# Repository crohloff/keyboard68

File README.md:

# keyboard68

## Production files
- The gerber files can be used with any manufacturer
- position files are meant to be used with jlcpcb and are already changed accordingly

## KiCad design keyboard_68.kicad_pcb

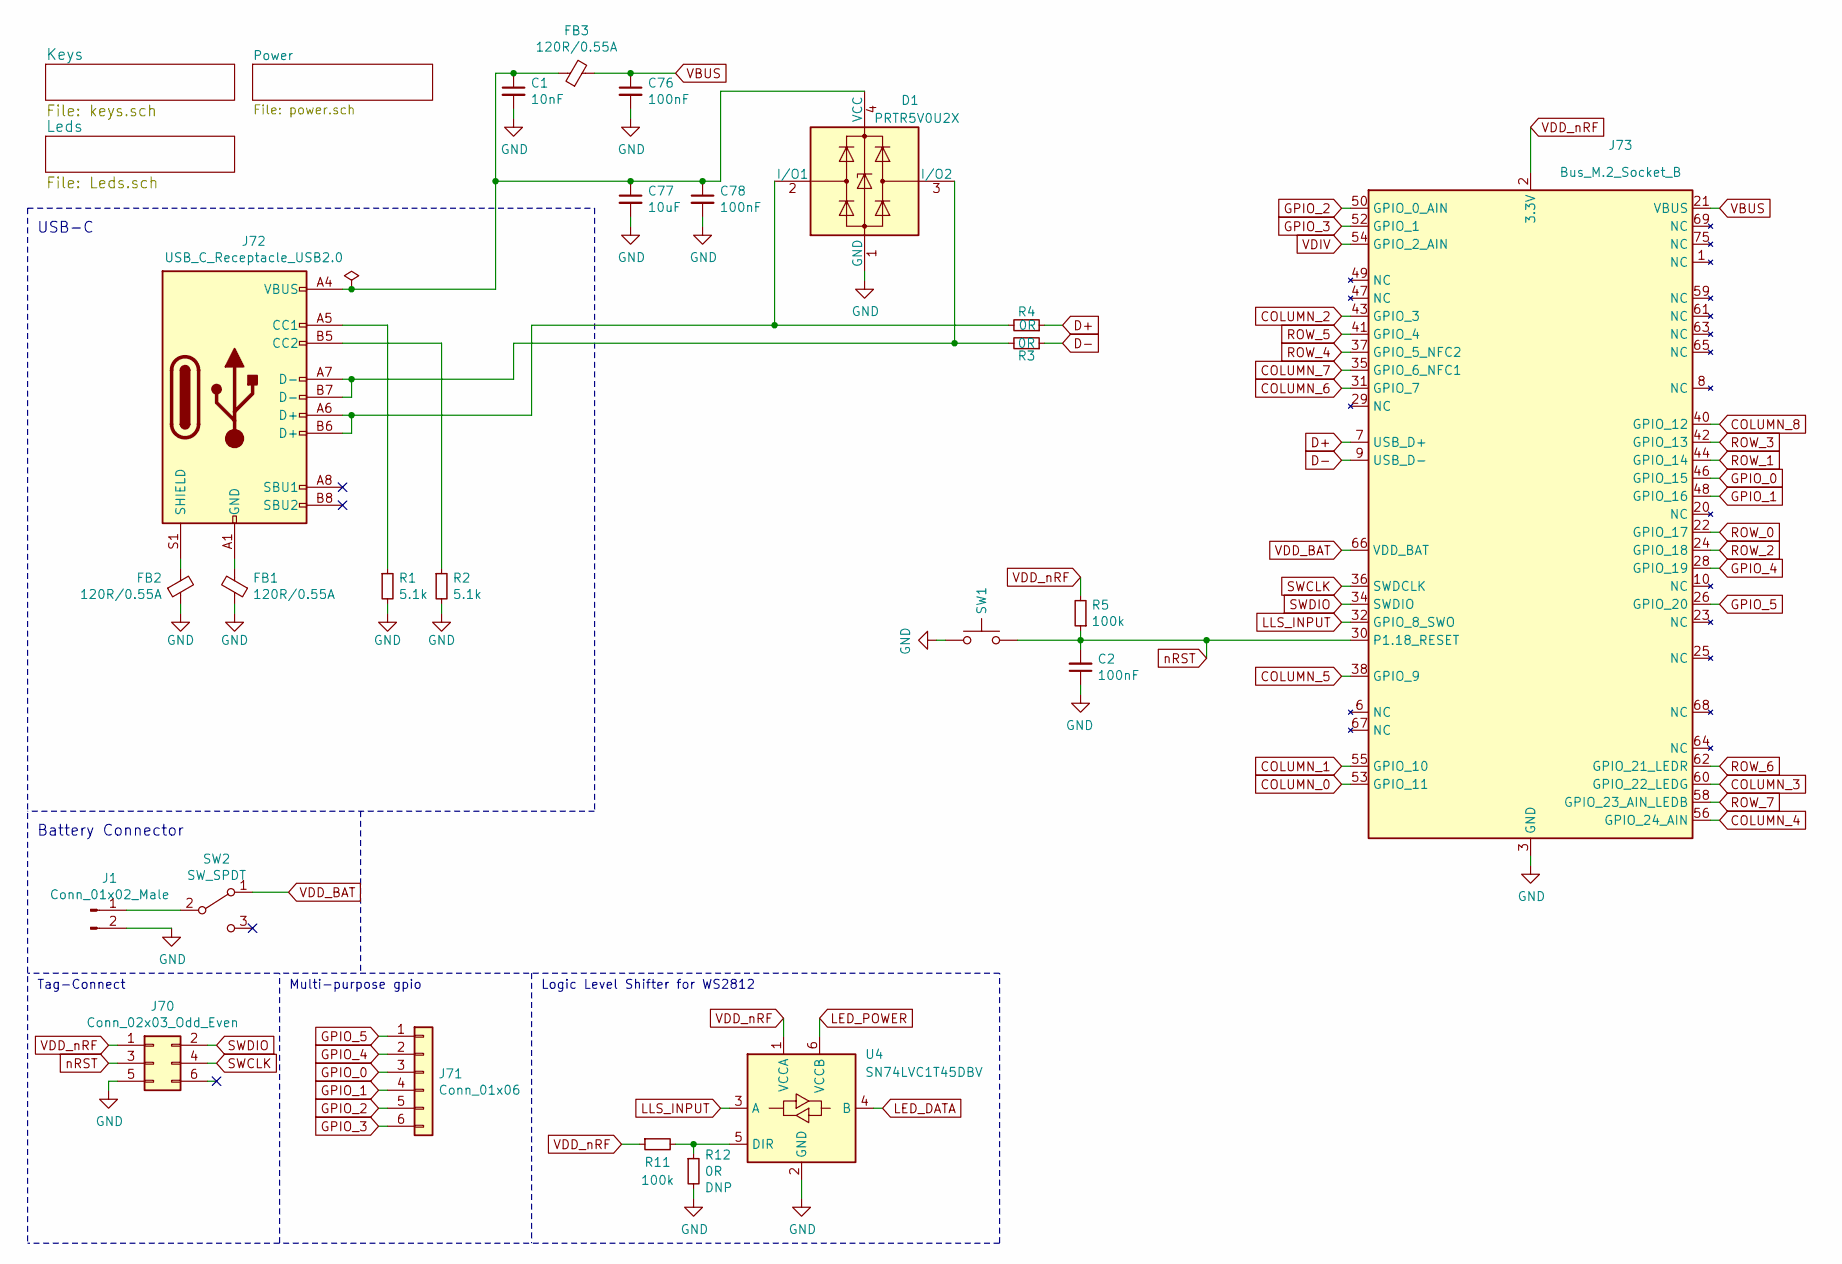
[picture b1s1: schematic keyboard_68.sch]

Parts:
C1: 10nF; C_0805_2012Metric; LCSC C83170
C2, C76, C78: 100nF; C_0805_2012Metric; LCSC C38141
C77: 10uF; C_0805_2012Metric; LCSC C307523
D1: PRTR5V0U2X; SOT-143; LCSC C330092
FB1, FB2, FB3: 120R/0.55A; L_0402_1005Metric; LCSC C85812
J1: Conn_01x02_Male; JST_PH_S2B-PH-SM4-TB_LF__SN_; MPN S2B-PH-SM4-TB(LF)(SN); DigiKey 455-1749-1-ND
J70: Conn_02x03_Odd_Even; Tag-Connect_TC2030-IDC-NL_2x03_P1.27mm_Vertical
J71: Conn_01x06; PinHeader_1x06_P2.54mm_Horizontal
J72: USB_C_Receptacle_USB2.0; USB_C_China; MPN U262-161N-4BVC11; LCSC C319148
J73: Bus_M.2_Socket_B; te_connectivity_121991190
R1, R2: 5.1k; R_0805_2012Metric; LCSC C84375
R3, R4, R12: 0R; R_0805_2012Metric; LCSC C96345
R5, R11: 100k; R_0805_2012Metric; LCSC C96346
SW1: EVQPUJ02K / EVQPUA02K; Panasonic_EVQPUJ_EVQPUA; MPN EVQ-PUJ02K; DigiKey P10851SCT-ND
SW2: SW_SPDT; SW_SPDT_CK-JS102011SAQN; MPN JS102011SAQN; DigiKey 401-1999-1-ND
U4: SN74LVC1T45DBV; SOT-23-6; MPN SN74LVC1T45DBVT; Digikey 296-30381-1-ND

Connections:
COLUMN_0: J73.53 (GPIO_11); also elsewhere on the board
COLUMN_1: J73.55 (GPIO_10); also elsewhere on the board
COLUMN_2: J73.43 (GPIO_3); also elsewhere on the board
COLUMN_3: J73.60 (GPIO_22_LEDG); also elsewhere on the board
COLUMN_4: J73.56 (GPIO_24_AIN); also elsewhere on the board
COLUMN_5: J73.38 (GPIO_9); also elsewhere on the board
COLUMN_6: J73.31 (GPIO_7); also elsewhere on the board
COLUMN_7: J73.35 (GPIO_6_NFC1); also elsewhere on the board
COLUMN_8: J73.40 (GPIO_12); also elsewhere on the board
D+: J73.7 (USB_D+), R4.1
D-: J73.9 (USB_D-), R3.1
GND: C1.2, C2.1, C76.2, C77.2, C78.2, D1.1 (GND), FB1.1, FB2.1, J1.2, J70.5, J73.3 (GND), J73.5 (GND), J73.11 (GND), J73.27 (GND), J73.33 (GND), J73.39 (GND), J73.45 (GND), J73.51 (GND), J73.57 (GND), J73.71 (GND), J73.73 (GND), R1.2, R2.2, R12.2, SW1.1, U4.2 (GND); also elsewhere on the board
GPIO_0: J71.3, J73.46 (GPIO_15)
GPIO_1: J71.4, J73.48 (GPIO_16)
GPIO_2: J71.5, J73.50 (GPIO_0_AIN)
GPIO_3: J71.6, J73.52 (GPIO_1)
GPIO_4: J71.2, J73.28 (GPIO_19)
GPIO_5: J71.1, J73.26 (GPIO_20)
LED_DATA: U4.4 (B); also elsewhere on the board
LED_POWER: U4.6 (VCCB); also elsewhere on the board
unnamed: C1.1, C77.1, C78.1, D1.4 (VCC), FB3.1, J72.A4 (VBUS), J72.A9 (VBUS), J72.B4 (VBUS), J72.B9 (VBUS)
unnamed: D1.2 (I/O1), J72.A6 (D+), J72.B6 (D+), R4.2
unnamed: D1.3 (I/O2), J72.A7 (D-), J72.B7 (D-), R3.2
unnamed: FB1.2, J72.A1 (GND), J72.A12 (GND), J72.B1 (GND), J72.B12 (GND)
unnamed: FB2.2, J72.S1 (SHIELD)
unnamed: J1.1, SW2.2 (B)
unnamed: J72.A5 (CC1), R1.1
unnamed: J72.B5 (CC2), R2.1
ROW_0: J73.22 (GPIO_17); also elsewhere on the board
ROW_1: J73.44 (GPIO_14); also elsewhere on the board
ROW_2: J73.24 (GPIO_18); also elsewhere on the board
ROW_3: J73.42 (GPIO_13); also elsewhere on the board
ROW_4: J73.37 (GPIO_5_NFC2); also elsewhere on the board
ROW_5: J73.41 (GPIO_4); also elsewhere on the board
ROW_6: J73.62 (GPIO_21_LEDR); also elsewhere on the board
ROW_7: J73.58 (GPIO_23_AIN_LEDB); also elsewhere on the board
SWCLK: J70.4, J73.36 (SWDCLK)
SWDIO: J70.2, J73.34 (SWDIO)
VBUS: C76.1, FB3.2, J73.21 (VBUS); also elsewhere on the board
VDD_BAT: J73.66 (VDD_BAT), SW2.1 (A); also elsewhere on the board
VDD_nRF: J70.1, J73.2 (3.3V), J73.4 (3.3V), J73.70 (3.3V), J73.72 (3.3V), J73.74 (3.3V), R5.2, R11.1, U4.1 (VCCA)
VDIV: J73.54 (GPIO_2_AIN); also elsewhere on the board
nRST: C2.2, J70.3, J73.30 (P1.18_RESET), R5.1, SW1.2

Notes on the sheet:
Battery Connector
USB-C
Tag-Connect
Multi-purpose gpio
Logic Level Shifter for WS2812

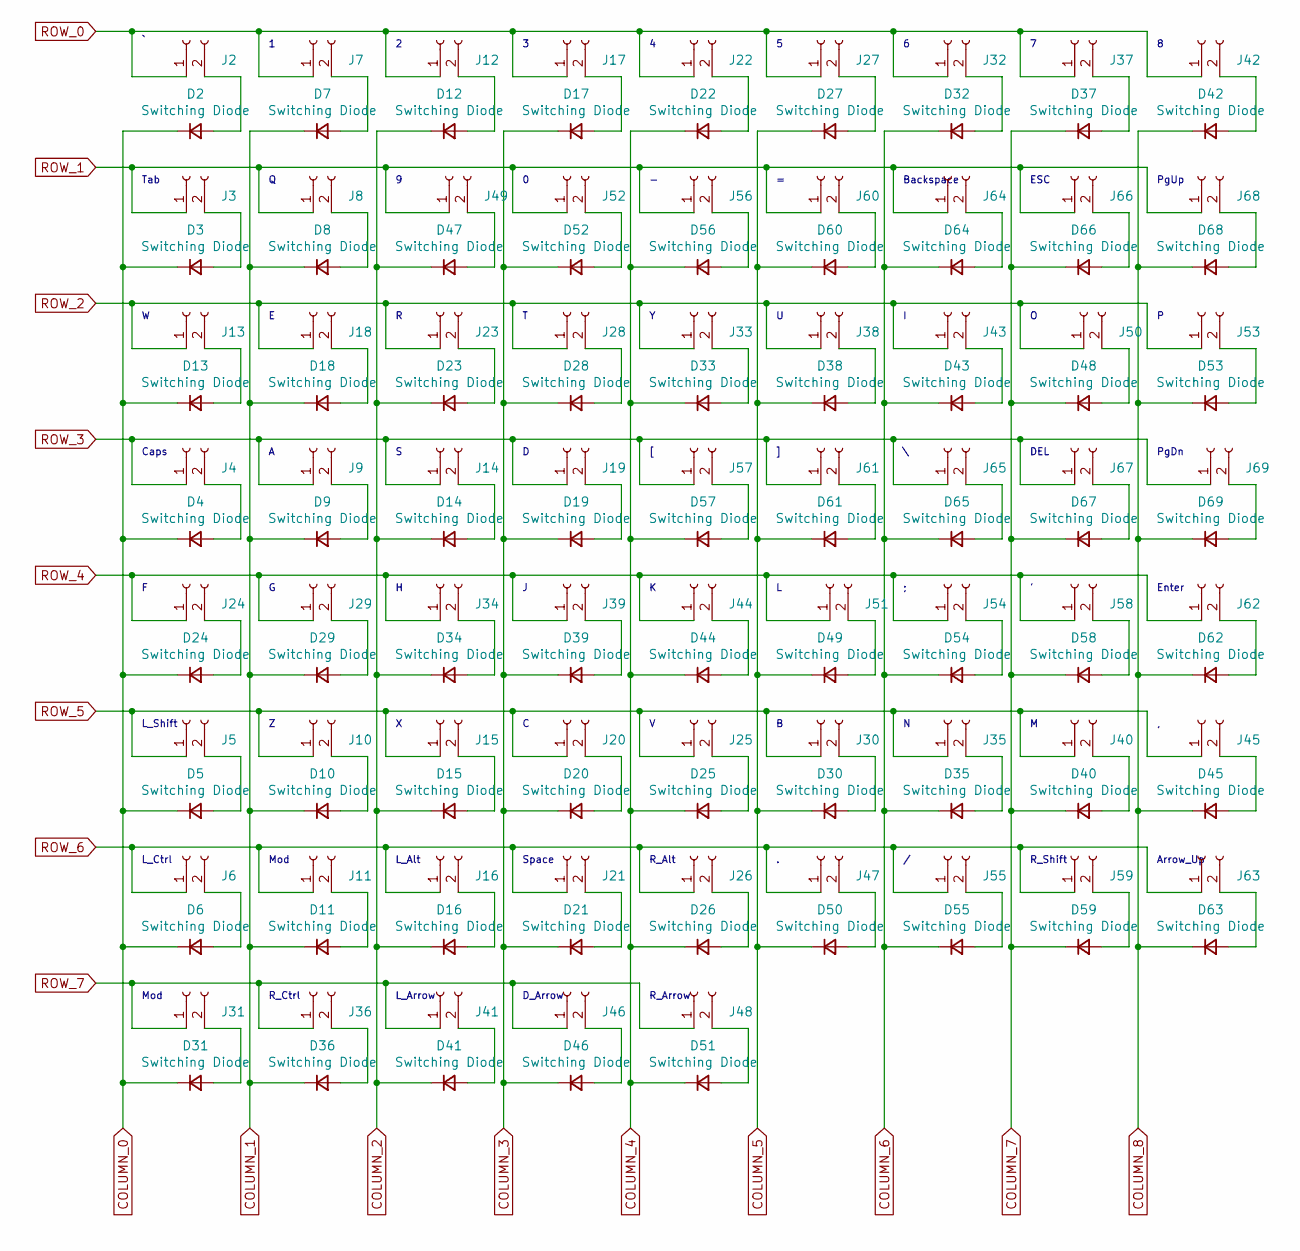
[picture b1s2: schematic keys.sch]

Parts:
D2, D3, D4, D5, D6, D7, D8, D9, D10, D11, D12, D13, D14, D15, D16, D17, D18, D19, D20, D21, D22, D23, D24, D25, D26, D27, D28, D29, D30, D31, D32, D33, D34, D35, D36, D37, D38, D39, D40, D41, D42, D43, D44, D45, D46, D47, D48, D49, D50, D51, D52, D53, D54, D55, D56, D57, D58, D59, D60, D61, D62, D63, D64, D65, D66, D67, D68, D69: Switching Diode; D_0805_2012Metric; LCSC C109001
J2, J3, J4, J5, J6, J7, J8, J9, J10, J11, J12, J13, J14, J15, J16, J17, J18, J19, J20, J21, J22, J23, J24, J25, J26, J27, J28, J29, J30, J31, J32, J33, J34, J35, J36, J37, J38, J39, J40, J41, J42, J43, J44, J45, J46, J47, J48, J49, J50, J51, J52, J53, J54, J55, J56, J57, J58, J59, J60, J61, J62, J63, J64, J65, J66, J67, J68, J69: Conn_01x02_Female; Kaihl_socket_CPG151101S11

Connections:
COLUMN_0: D2.1 (K), D3.1 (K), D4.1 (K), D5.1 (K), D6.1 (K), D13.1 (K), D24.1 (K), D31.1 (K); also elsewhere on the board
COLUMN_1: D7.1 (K), D8.1 (K), D9.1 (K), D10.1 (K), D11.1 (K), D18.1 (K), D29.1 (K), D36.1 (K); also elsewhere on the board
COLUMN_2: D12.1 (K), D14.1 (K), D15.1 (K), D16.1 (K), D23.1 (K), D34.1 (K), D41.1 (K), D47.1 (K); also elsewhere on the board
COLUMN_3: D17.1 (K), D19.1 (K), D20.1 (K), D21.1 (K), D28.1 (K), D39.1 (K), D46.1 (K), D52.1 (K); also elsewhere on the board
COLUMN_4: D22.1 (K), D25.1 (K), D26.1 (K), D33.1 (K), D44.1 (K), D51.1 (K), D56.1 (K), D57.1 (K); also elsewhere on the board
COLUMN_5: D27.1 (K), D30.1 (K), D38.1 (K), D49.1 (K), D50.1 (K), D60.1 (K), D61.1 (K); also elsewhere on the board
COLUMN_6: D32.1 (K), D35.1 (K), D43.1 (K), D54.1 (K), D55.1 (K), D64.1 (K), D65.1 (K); also elsewhere on the board
COLUMN_7: D37.1 (K), D40.1 (K), D48.1 (K), D58.1 (K), D59.1 (K), D66.1 (K), D67.1 (K); also elsewhere on the board
COLUMN_8: D42.1 (K), D45.1 (K), D53.1 (K), D62.1 (K), D63.1 (K), D68.1 (K), D69.1 (K); also elsewhere on the board
unnamed: D2.2 (A), J2.2
unnamed: D3.2 (A), J3.2
unnamed: D4.2 (A), J4.2
unnamed: D5.2 (A), J5.2
unnamed: D6.2 (A), J6.2
unnamed: D7.2 (A), J7.2
unnamed: D8.2 (A), J8.2
unnamed: D9.2 (A), J9.2
unnamed: D10.2 (A), J10.2
unnamed: D11.2 (A), J11.2
unnamed: D12.2 (A), J12.2
unnamed: D13.2 (A), J13.2
unnamed: D14.2 (A), J14.2
unnamed: D15.2 (A), J15.2
unnamed: D16.2 (A), J16.2
unnamed: D17.2 (A), J17.2
unnamed: D18.2 (A), J18.2
unnamed: D19.2 (A), J19.2
unnamed: D20.2 (A), J20.2
unnamed: D21.2 (A), J21.2
unnamed: D22.2 (A), J22.2
unnamed: D23.2 (A), J23.2
unnamed: D24.2 (A), J24.2
unnamed: D25.2 (A), J25.2
unnamed: D26.2 (A), J26.2
unnamed: D27.2 (A), J27.2
unnamed: D28.2 (A), J28.2
unnamed: D29.2 (A), J29.2
unnamed: D30.2 (A), J30.2
unnamed: D31.2 (A), J31.2
unnamed: D32.2 (A), J32.2
unnamed: D33.2 (A), J33.2
unnamed: D34.2 (A), J34.2
unnamed: D35.2 (A), J35.2
unnamed: D36.2 (A), J36.2
unnamed: D37.2 (A), J37.2
unnamed: D38.2 (A), J38.2
unnamed: D39.2 (A), J39.2
unnamed: D40.2 (A), J40.2
unnamed: D41.2 (A), J41.2
unnamed: D42.2 (A), J42.2
unnamed: D43.2 (A), J43.2
unnamed: D44.2 (A), J44.2
unnamed: D45.2 (A), J45.2
unnamed: D46.2 (A), J46.2
unnamed: D47.2 (A), J49.2
unnamed: D48.2 (A), J50.2
unnamed: D49.2 (A), J51.2
unnamed: D50.2 (A), J47.2
unnamed: D51.2 (A), J48.2
unnamed: D52.2 (A), J52.2
unnamed: D53.2 (A), J53.2
unnamed: D54.2 (A), J54.2
unnamed: D55.2 (A), J55.2
unnamed: D56.2 (A), J56.2
unnamed: D57.2 (A), J57.2
unnamed: D58.2 (A), J58.2
unnamed: D59.2 (A), J59.2
unnamed: D60.2 (A), J60.2
unnamed: D61.2 (A), J61.2
unnamed: D62.2 (A), J62.2
unnamed: D63.2 (A), J63.2
unnamed: D64.2 (A), J64.2
unnamed: D65.2 (A), J65.2
unnamed: D66.2 (A), J66.2
unnamed: D67.2 (A), J67.2
unnamed: D68.2 (A), J68.2
unnamed: D69.2 (A), J69.2
ROW_0: J2.1, J7.1, J12.1, J17.1, J22.1, J27.1, J32.1, J37.1, J42.1; also elsewhere on the board
ROW_1: J3.1, J8.1, J49.1, J52.1, J56.1, J60.1, J64.1, J66.1, J68.1; also elsewhere on the board
ROW_2: J13.1, J18.1, J23.1, J28.1, J33.1, J38.1, J43.1, J50.1, J53.1; also elsewhere on the board
ROW_3: J4.1, J9.1, J14.1, J19.1, J57.1, J61.1, J65.1, J67.1, J69.1; also elsewhere on the board
ROW_4: J24.1, J29.1, J34.1, J39.1, J44.1, J51.1, J54.1, J58.1, J62.1; also elsewhere on the board
ROW_5: J5.1, J10.1, J15.1, J20.1, J25.1, J30.1, J35.1, J40.1, J45.1; also elsewhere on the board
ROW_6: J6.1, J11.1, J16.1, J21.1, J26.1, J47.1, J55.1, J59.1, J63.1; also elsewhere on the board
ROW_7: J31.1, J36.1, J41.1, J46.1, J48.1; also elsewhere on the board

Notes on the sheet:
PgUp
ESC
Backspace
Tab
Caps
L_Shift
Space
L_Alt
L_Ctrl
Mod
L_Arrow
D_Arrow
R_Arrow
Enter
Arrow_Up
PgDn
DEL
R_Ctrl
R_Alt
R_Shift

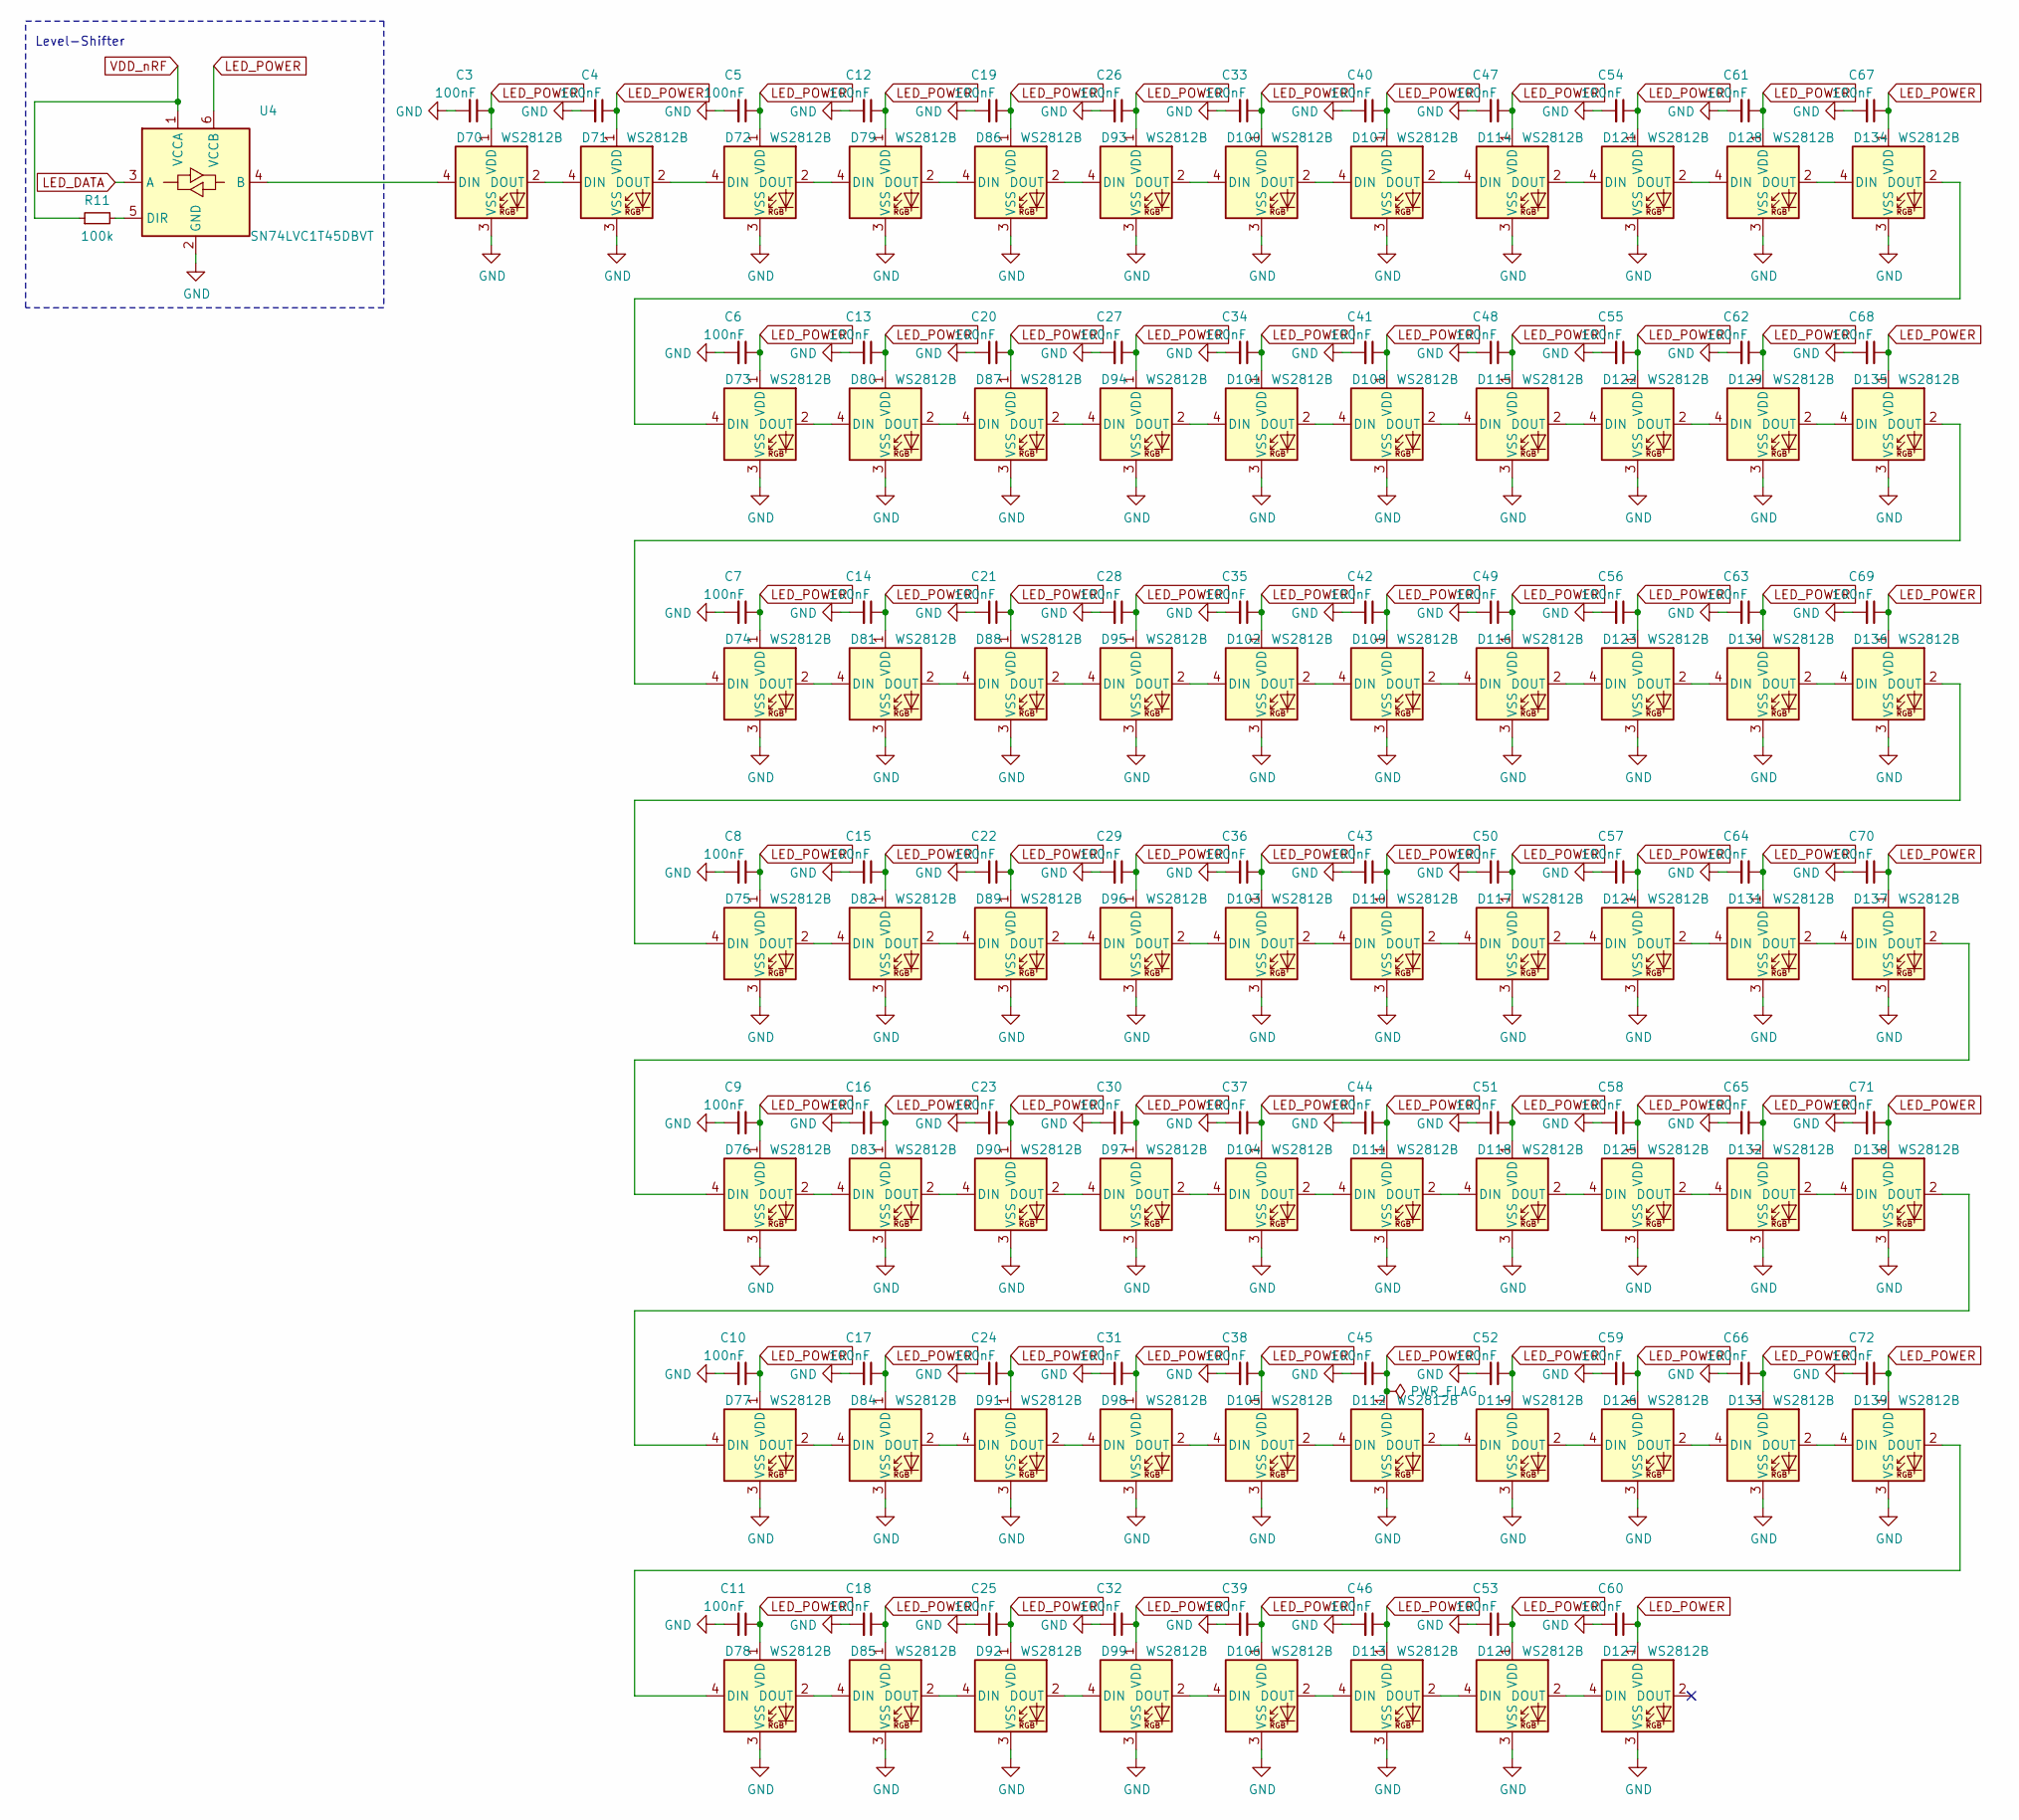
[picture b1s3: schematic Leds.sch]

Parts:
C3, C4, C5, C6, C7, C8, C9, C10, C11, C12, C13, C14, C15, C16, C17, C18, C19, C20, C21, C22, C23, C24, C25, C26, C27, C28, C29, C30, C31, C32, C33, C34, C35, C36, C37, C38, C39, C40, C41, C42, C43, C44, C45, C46, C47, C48, C49, C50, C51, C52, C53, C54, C55, C56, C57, C58, C59, C60, C61, C62, C63, C64, C65, C66, C67, C68, C69, C70, C71, C72: 100nF; C_0805_2012Metric; LCSC C38141
D70, D71: WS2812B; LED_WS2812B_PLCC4_5.0x5.0mm_P3.2mm; LCSC C114585
D72, D73, D74, D75, D76, D77, D78, D79, D80, D81, D82, D83, D84, D85, D86, D87, D88, D89, D90, D91, D92, D93, D94, D95, D96, D97, D98, D99, D100, D101, D102, D103, D104, D105, D106, D107, D108, D109, D110, D111, D112, D113, D114, D115, D116, D117, D118, D119, D120, D121, D122, D123, D124, D125, D126, D127, D128, D129, D130, D131, D132, D133, D134, D135, D136, D137, D138, D139: WS2812B; ws2812_inPCB; LCSC C114585
R11: 100k; R_0805_2012Metric
U4: SN74LVC1T45DBVT; SOT-23-6

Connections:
GND: C3.2, C4.2, C5.2, C6.2, C7.2, C8.2, C9.2, C10.2, C11.2, C12.2, C13.2, C14.2, C15.2, C16.2, C17.2, C18.2, C19.2, C20.2, C21.2, C22.2, C23.2, C24.2, C25.2, C26.2, C27.2, C28.2, C29.2, C30.2, C31.2, C32.2, C33.2, C34.2, C35.2, C36.2, C37.2, C38.2, C39.2, C40.2, C41.2, C42.2, C43.2, C44.2, C45.2, C46.2, C47.2, C48.2, C49.2, C50.2, C51.2, C52.2, C53.2, C54.2, C55.2, C56.2, C57.2, C58.2, C59.2, C60.2, C61.2, C62.2, C63.2, C64.2, C65.2, C66.2, C67.2, C68.2, C69.2, C70.2, C71.2, C72.2, D70.3 (VSS), D71.3 (VSS), D72.3 (VSS), D73.3 (VSS), D74.3 (VSS), D75.3 (VSS), D76.3 (VSS), D77.3 (VSS), D78.3 (VSS), D79.3 (VSS), D80.3 (VSS), D81.3 (VSS), D82.3 (VSS), D83.3 (VSS), D84.3 (VSS), D85.3 (VSS), D86.3 (VSS), D87.3 (VSS), D88.3 (VSS), D89.3 (VSS), D90.3 (VSS), D91.3 (VSS), D92.3 (VSS), D93.3 (VSS), D94.3 (VSS), D95.3 (VSS), D96.3 (VSS), D97.3 (VSS), D98.3 (VSS), D99.3 (VSS), D100.3 (VSS), D101.3 (VSS), D102.3 (VSS), D103.3 (VSS), D104.3 (VSS), D105.3 (VSS), D106.3 (VSS), D107.3 (VSS), D108.3 (VSS), D109.3 (VSS), D110.3 (VSS), D111.3 (VSS), D112.3 (VSS), D113.3 (VSS), D114.3 (VSS), D115.3 (VSS), D116.3 (VSS), D117.3 (VSS), D118.3 (VSS), D119.3 (VSS), D120.3 (VSS), D121.3 (VSS), D122.3 (VSS), D123.3 (VSS), D124.3 (VSS), D125.3 (VSS), D126.3 (VSS), D127.3 (VSS), D128.3 (VSS), D129.3 (VSS), D130.3 (VSS), D131.3 (VSS), D132.3 (VSS), D133.3 (VSS), D134.3 (VSS), D135.3 (VSS), D136.3 (VSS), D137.3 (VSS), D138.3 (VSS), D139.3 (VSS), U4.2 (GND); also elsewhere on the board
LED_DATA: D70.4 (DIN), U4.4 (B)
LED_POWER: C3.1, C4.1, C5.1, C6.1, C7.1, C8.1, C9.1, C10.1, C11.1, C12.1, C13.1, C14.1, C15.1, C16.1, C17.1, C18.1, C19.1, C20.1, C21.1, C22.1, C23.1, C24.1, C25.1, C26.1, C27.1, C28.1, C29.1, C30.1, C31.1, C32.1, C33.1, C34.1, C35.1, C36.1, C37.1, C38.1, C39.1, C40.1, C41.1, C42.1, C43.1, C44.1, C45.1, C46.1, C47.1, C48.1, C49.1, C50.1, C51.1, C52.1, C53.1, C54.1, C55.1, C56.1, C57.1, C58.1, C59.1, C60.1, C61.1, C62.1, C63.1, C64.1, C65.1, C66.1, C67.1, C68.1, C69.1, C70.1, C71.1, C72.1, D70.1 (VDD), D71.1 (VDD), D72.1 (VDD), D73.1 (VDD), D74.1 (VDD), D75.1 (VDD), D76.1 (VDD), D77.1 (VDD), D78.1 (VDD), D79.1 (VDD), D80.1 (VDD), D81.1 (VDD), D82.1 (VDD), D83.1 (VDD), D84.1 (VDD), D85.1 (VDD), D86.1 (VDD), D87.1 (VDD), D88.1 (VDD), D89.1 (VDD), D90.1 (VDD), D91.1 (VDD), D92.1 (VDD), D93.1 (VDD), D94.1 (VDD), D95.1 (VDD), D96.1 (VDD), D97.1 (VDD), D98.1 (VDD), D99.1 (VDD), D100.1 (VDD), D101.1 (VDD), D102.1 (VDD), D103.1 (VDD), D104.1 (VDD), D105.1 (VDD), D106.1 (VDD), D107.1 (VDD), D108.1 (VDD), D109.1 (VDD), D110.1 (VDD), D111.1 (VDD), D112.1 (VDD), D113.1 (VDD), D114.1 (VDD), D115.1 (VDD), D116.1 (VDD), D117.1 (VDD), D118.1 (VDD), D119.1 (VDD), D120.1 (VDD), D121.1 (VDD), D122.1 (VDD), D123.1 (VDD), D124.1 (VDD), D125.1 (VDD), D126.1 (VDD), D127.1 (VDD), D128.1 (VDD), D129.1 (VDD), D130.1 (VDD), D131.1 (VDD), D132.1 (VDD), D133.1 (VDD), D134.1 (VDD), D135.1 (VDD), D136.1 (VDD), D137.1 (VDD), D138.1 (VDD), D139.1 (VDD), U4.6 (VCCB); also elsewhere on the board
unnamed: D70.2 (DOUT), D71.4 (DIN)
unnamed: D71.2 (DOUT), D72.4 (DIN)
unnamed: D72.2 (DOUT), D79.4 (DIN)
unnamed: D73.2 (DOUT), D80.4 (DIN)
unnamed: D74.2 (DOUT), D81.4 (DIN)
unnamed: D75.2 (DOUT), D82.4 (DIN)
unnamed: D76.2 (DOUT), D83.4 (DIN)
unnamed: D77.2 (DOUT), D84.4 (DIN)
unnamed: D78.2 (DOUT), D85.4 (DIN)
unnamed: D79.2 (DOUT), D86.4 (DIN)
unnamed: D80.2 (DOUT), D87.4 (DIN)
unnamed: D81.2 (DOUT), D88.4 (DIN)
unnamed: D82.2 (DOUT), D89.4 (DIN)
unnamed: D83.2 (DOUT), D90.4 (DIN)
unnamed: D84.2 (DOUT), D91.4 (DIN)
unnamed: D85.2 (DOUT), D92.4 (DIN)
unnamed: D86.2 (DOUT), D93.4 (DIN)
unnamed: D87.2 (DOUT), D94.4 (DIN)
unnamed: D88.2 (DOUT), D95.4 (DIN)
unnamed: D89.2 (DOUT), D96.4 (DIN)
unnamed: D90.2 (DOUT), D97.4 (DIN)
unnamed: D91.2 (DOUT), D98.4 (DIN)
unnamed: D92.2 (DOUT), D99.4 (DIN)
unnamed: D100.2 (DOUT), D107.4 (DIN)
unnamed: D93.2 (DOUT), D100.4 (DIN)
unnamed: D101.2 (DOUT), D108.4 (DIN)
unnamed: D94.2 (DOUT), D101.4 (DIN)
unnamed: D102.2 (DOUT), D109.4 (DIN)
unnamed: D95.2 (DOUT), D102.4 (DIN)
unnamed: D103.2 (DOUT), D110.4 (DIN)
unnamed: D96.2 (DOUT), D103.4 (DIN)
unnamed: D104.2 (DOUT), D111.4 (DIN)
unnamed: D97.2 (DOUT), D104.4 (DIN)
unnamed: D105.2 (DOUT), D112.4 (DIN)
unnamed: D98.2 (DOUT), D105.4 (DIN)
unnamed: D106.2 (DOUT), D113.4 (DIN)
unnamed: D99.2 (DOUT), D106.4 (DIN)
unnamed: D107.2 (DOUT), D114.4 (DIN)
unnamed: D108.2 (DOUT), D115.4 (DIN)
unnamed: D109.2 (DOUT), D116.4 (DIN)
unnamed: D110.2 (DOUT), D117.4 (DIN)
unnamed: D111.2 (DOUT), D118.4 (DIN)
unnamed: D112.2 (DOUT), D119.4 (DIN)
unnamed: D113.2 (DOUT), D120.4 (DIN)
unnamed: D114.2 (DOUT), D121.4 (DIN)
unnamed: D115.2 (DOUT), D122.4 (DIN)
unnamed: D116.2 (DOUT), D123.4 (DIN)
unnamed: D117.2 (DOUT), D124.4 (DIN)
unnamed: D118.2 (DOUT), D125.4 (DIN)
unnamed: D119.2 (DOUT), D126.4 (DIN)
unnamed: D120.2 (DOUT), D127.4 (DIN)
unnamed: D121.2 (DOUT), D128.4 (DIN)
unnamed: D122.2 (DOUT), D129.4 (DIN)
unnamed: D123.2 (DOUT), D130.4 (DIN)
unnamed: D124.2 (DOUT), D131.4 (DIN)
unnamed: D125.2 (DOUT), D132.4 (DIN)
unnamed: D126.2 (DOUT), D133.4 (DIN)
unnamed: D128.2 (DOUT), D134.4 (DIN)
unnamed: D129.2 (DOUT), D135.4 (DIN)
unnamed: D130.2 (DOUT), D136.4 (DIN)
unnamed: D131.2 (DOUT), D137.4 (DIN)
unnamed: D132.2 (DOUT), D138.4 (DIN)
unnamed: D133.2 (DOUT), D139.4 (DIN)
unnamed: D73.4 (DIN), D134.2 (DOUT)
unnamed: D74.4 (DIN), D135.2 (DOUT)
unnamed: D75.4 (DIN), D136.2 (DOUT)
unnamed: D76.4 (DIN), D137.2 (DOUT)
unnamed: D77.4 (DIN), D138.2 (DOUT)
unnamed: D78.4 (DIN), D139.2 (DOUT)
VDD_nRF: R11.1, U4.1 (VCCA); also elsewhere on the board

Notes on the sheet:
Level-Shifter

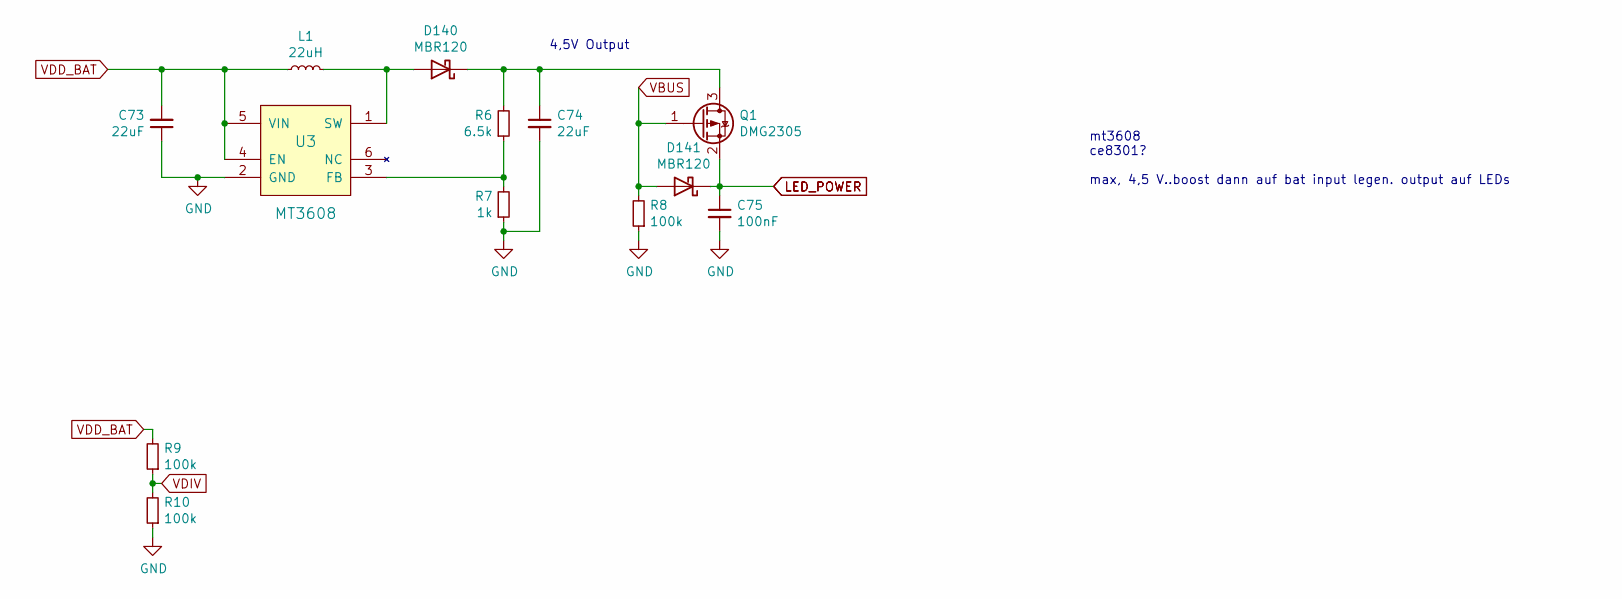
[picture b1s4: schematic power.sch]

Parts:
C73, C74: 22uF; C_0805_2012Metric; LCSC C86816
C75: 100nF; C_0805_2012Metric; LCSC C38141
D140, D141: MBR120; D_SOD-123; LCSC C81143
L1: 22uH; L_3x3_H1.5; MPN LVS303015-220M-N; LCSC C285838
Q1: DMG2305; SOT-23; LCSC C144153
R6: 6.5k; R_0805_2012Metric; LCSC C228968
R7: 1k; R_0805_2012Metric; LCSC C140870
R8, R9, R10: 100k; R_0805_2012Metric; LCSC C96346
U3: MT3608; SOT-23-6; LCSC C84817

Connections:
GND: C73.1, C74.2, C75.2, R7.1, R8.1, R10.1, U3.2 (GND); also elsewhere on the board
LED_POWER: C75.1, D141.1 (K), Q1.2 (S); also elsewhere on the board
unnamed: C74.1, D140.1 (K), Q1.3 (D), R6.2
unnamed: D140.2 (A), L1.2, U3.1 (SW)
unnamed: R6.1, R7.2, U3.3 (FB)
VBUS: D141.2 (A), Q1.1 (G), R8.2; also elsewhere on the board
VDD_BAT: C73.2, L1.1, R9.2, U3.4 (EN), U3.5 (VIN); also elsewhere on the board
VDIV: R9.1, R10.2; also elsewhere on the board

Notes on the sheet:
mt3608 ce8301? max, 4,5 V..boost dann auf bat input legen. output auf LEDs
4,5V Output

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
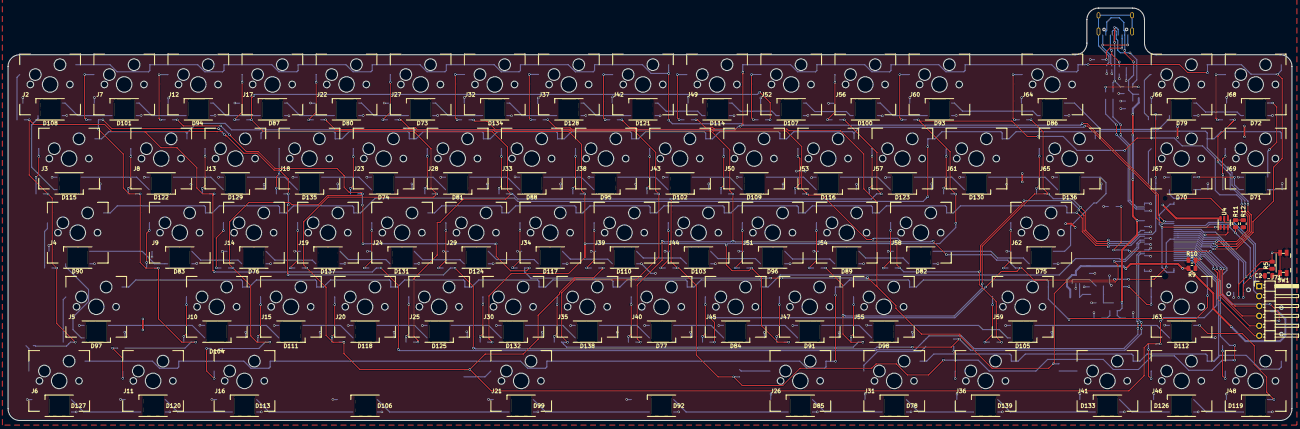
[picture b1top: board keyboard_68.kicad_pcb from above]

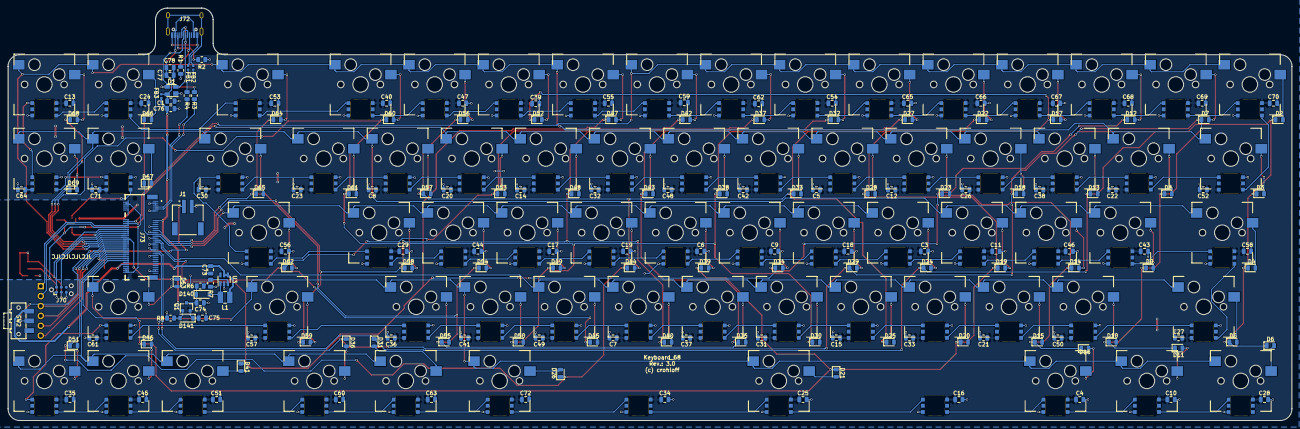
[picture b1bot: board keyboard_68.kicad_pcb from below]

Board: 2 copper layers, 330.0 x 106.0 mm, 313 parts (166 on the bottom side), 185 nets.

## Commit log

2019-07-23 initial project
2019-09-25 changed inductor and usb connector
2019-09-25 changed wrong partnumber of reset switch
2019-11-10 add 3d model for sidemount reset switch
2019-11-10 reset switch model added
2019-11-11 changed 3d model to virtual
2019-11-11 pulled usb connector out
2019-11-14 changed silk
2019-11-14 added dimensions, rotate battery conn
2019-11-15 added production files
2019-11-15 changed some value fields
2019-11-17 add LICENSE
2019-11-26 add notch for usb and cleanup
2019-11-26 add nrf52840 symbol and footprint
2019-11-26 add step model of nrf module
2019-11-26 place all components on backside
2019-11-26 page title etc
2020-01-15 add 3d model for switch
2020-01-15 add lls, switch and spare gpio connector
2020-02-02 change usb c connector, fix column 6
2020-02-02 switched to smaller module
2020-10-21 add level shifter for ws2812
2020-10-21 change logo place
2021-04-27 finalize for m.2 module
